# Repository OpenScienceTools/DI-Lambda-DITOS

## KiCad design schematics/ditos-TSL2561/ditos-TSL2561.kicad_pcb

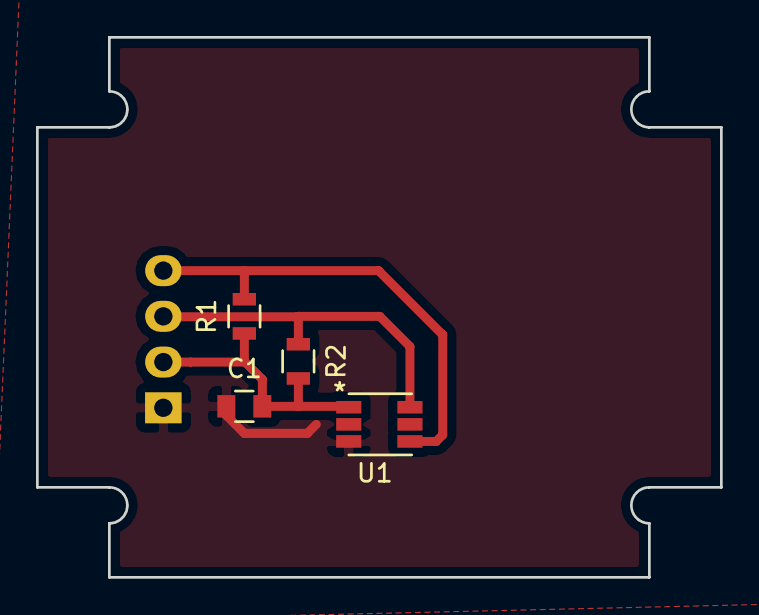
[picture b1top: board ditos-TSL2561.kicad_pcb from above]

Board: 2 copper layers, 38.0 x 30.0 mm, 5 parts (1 on the bottom side), 4 nets.

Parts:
C1: 1uF; C_0805
P1: CONN_01X04; Pin_Header_Straight_1x04
R1, R2: 4K7; R_0805
U1: TSL2561; TMB-6

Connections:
GND: C1.1, P1.1, U1.2, U1.3
unnamed: P1.3, R2.1, U1.6
unnamed: P1.4, R1.2, U1.4
VCC: C1.2, P1.2, R1.1, R2.2, U1.1

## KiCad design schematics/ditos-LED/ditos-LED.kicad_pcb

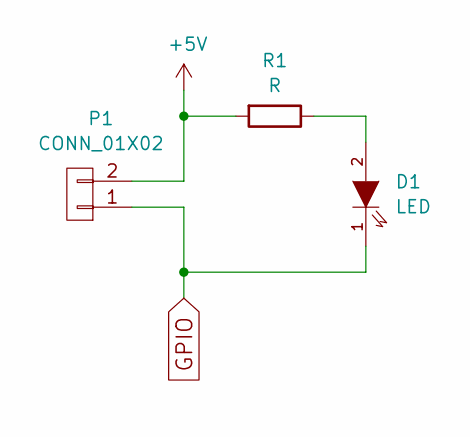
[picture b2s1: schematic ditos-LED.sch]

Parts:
D1: LED; LED-5MM
P1: CONN_01X02; Pin_Header_Straight_1x02
R1: R; Resistor_Horizontal_RM7mm

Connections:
unnamed: D1.1 (K), P1.1
unnamed: D1.2 (A), R1.1
unnamed: P1.2, R1.2

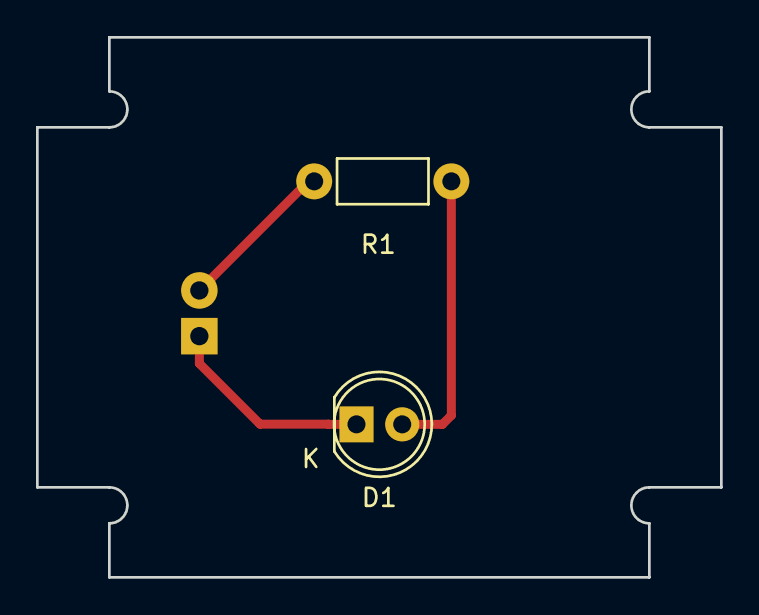
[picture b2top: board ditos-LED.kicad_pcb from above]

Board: 2 copper layers, 38.0 x 30.0 mm, 3 parts (1 on the bottom side), 3 nets.

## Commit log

2016-09-30 First release
